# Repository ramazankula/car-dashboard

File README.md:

# Renault Megane 2 Dashboard Panel Prototype for Vehicle Simulator
In this project, a clone of Renault Megane 2 car dashboard panel is designed specially for a vehicle simulator project. It was designed to be compatible with vehicel simulation software.

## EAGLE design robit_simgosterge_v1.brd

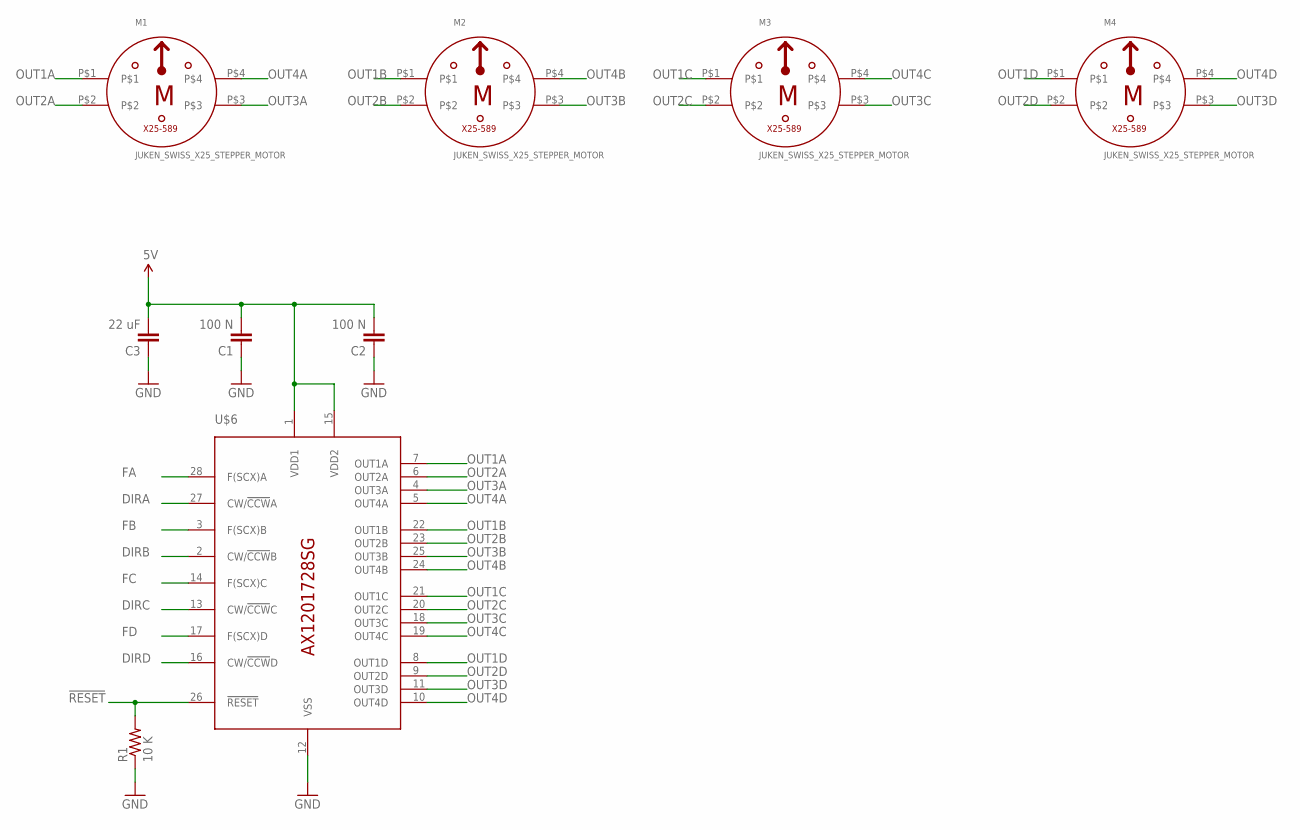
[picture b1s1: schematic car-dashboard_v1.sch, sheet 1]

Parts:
C1, C2: 100 N; C0805
C3: 22 uF; C0805
M1, M2, M3, M4: JUKEN_SWISS_X25_STEPPER_MOTOR; X25_STEPPER_MOTOR
R1: 10 K; 0805
U$6: AX1201728SG-X25_DRIVER; SOL-28

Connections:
5V: C1.2, C2.2, C3.2, U$6.1 (VDD1), U$6.15 (VDD2); also elsewhere on the board
!RESET: R1.2, U$6.26 (!RESET); also elsewhere on the board
DIRA: U$6.27 (CW/!CCW!A); also elsewhere on the board
DIRB: U$6.2 (CW/!CCW!B); also elsewhere on the board
DIRC: U$6.13 (CW/!CCW!C); also elsewhere on the board
DIRD: U$6.16 (CW/!CCW!D); also elsewhere on the board
FA: U$6.28 (F(SCX)A); also elsewhere on the board
FB: U$6.3 (F(SCX)B); also elsewhere on the board
FC: U$6.14 (F(SCX)C); also elsewhere on the board
FD: U$6.17 (F(SCX)D); also elsewhere on the board
GND: C1.1, C2.1, C3.1, R1.1, U$6.12 (VSS); also elsewhere on the board
OUT1A: M1.P$1, U$6.7 (OUT1A)
OUT1B: M2.P$1, U$6.22 (OUT1B)
OUT1C: M3.P$1, U$6.21 (OUT1C)
OUT1D: M4.P$1, U$6.8 (OUT1D)
OUT2A: M1.P$2, U$6.6 (OUT2A)
OUT2B: M2.P$2, U$6.23 (OUT2B)
OUT2C: M3.P$2, U$6.20 (OUT2C)
OUT2D: M4.P$2, U$6.9 (OUT2D)
OUT3A: M1.P$3, U$6.4 (OUT3A)
OUT3B: M2.P$3, U$6.25 (OUT3B)
OUT3C: M3.P$3, U$6.18 (OUT3C)
OUT3D: M4.P$3, U$6.11 (OUT3D)
OUT4A: M1.P$4, U$6.5 (OUT4A)
OUT4B: M2.P$4, U$6.24 (OUT4B)
OUT4C: M3.P$4, U$6.19 (OUT4C)
OUT4D: M4.P$4, U$6.10 (OUT4D)

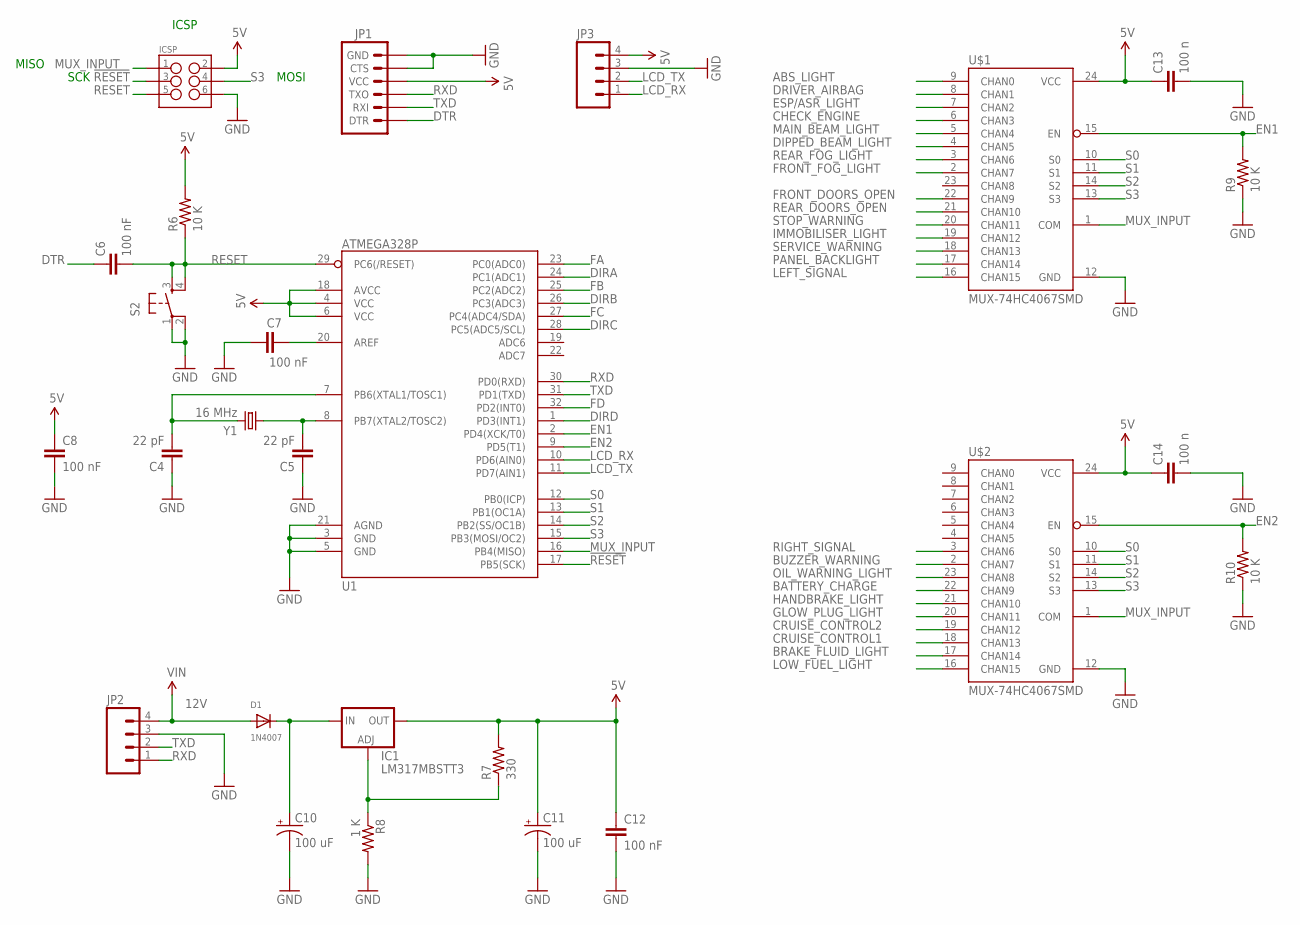
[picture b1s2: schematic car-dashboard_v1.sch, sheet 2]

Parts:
C4, C5: 22 pF; C0805
C6, C7, C8, C12: 100 nF; C0805
C10, C11: 100 uF; PANASONIC_F
C13, C14: 100 n; C0805
D1: 1N4007; SMADIODE
IC1: LM317MBSTT3; SOT223
ICSP: M03X22X3_SILK_SM; 2X3
JP1: ARDUINO_SERIAL_PROGRAMPTH; 1X06
JP2, JP3: M04POLAR; MOLEX-1X4
R6, R9, R10: 10 K; R0805
R7: 330; R0805
R8: 1 K; R0805
S2: TAC_SWITCHPTH; TACTILE-PTH
U1: ATMEGA328P; TQFP32-08
U$1, U$2: MUX-74HC4067SMD; SSOP24
Y1: 16 MHz; HC49UP

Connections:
5V: C8.1, C11.+, C12.1, C13.1, C14.1, IC1.4 (OUT), ICSP.2, JP1.4 (VCC), JP3.4, R6.2, R7.2, U1.4 (VCC), U1.6 (VCC), U1.18 (AVCC), U$1.24 (VCC), U$2.24 (VCC); also elsewhere on the board
12V: D1.A, JP2.4
!RESET: ICSP.3, U1.17 (PB5(SCK)); also elsewhere on the board
ABS_LIGHT: U$1.9 (CHAN0); also elsewhere on the board
BATTERY_CHARGE: U$2.22 (CHAN9); also elsewhere on the board
BRAKE_FLUID_LIGHT: U$2.17 (CHAN14); also elsewhere on the board
BUZZER_WARNING: U$2.2 (CHAN7); also elsewhere on the board
CHECK_ENGINE: U$1.6 (CHAN3); also elsewhere on the board
CRUISE_CONTROL1: U$2.18 (CHAN13); also elsewhere on the board
CRUISE_CONTROL2: U$2.19 (CHAN12); also elsewhere on the board
DIPPED_BEAM_LIGHT: U$1.4 (CHAN5); also elsewhere on the board
DIRA: U1.24 (PC1(ADC1)); also elsewhere on the board
DIRB: U1.26 (PC3(ADC3)); also elsewhere on the board
DIRC: U1.28 (PC5(ADC5/SCL)); also elsewhere on the board
DIRD: U1.1 (PD3(INT1)); also elsewhere on the board
DRIVER_AIRBAG: U$1.8 (CHAN1); also elsewhere on the board
DTR: C6.1, JP1.1 (DTR)
EN1: R9.2, U1.2 (PD4(XCK/T0)), U$1.15 (EN)
EN2: R10.2, U1.9 (PD5(T1)), U$2.15 (EN)
ESP/ASR_LIGHT: U$1.7 (CHAN2); also elsewhere on the board
FA: U1.23 (PC0(ADC0)); also elsewhere on the board
FB: U1.25 (PC2(ADC2)); also elsewhere on the board
FC: U1.27 (PC4(ADC4/SDA)); also elsewhere on the board
FD: U1.32 (PD2(INT0)); also elsewhere on the board
FRONT_DOORS_OPEN: U$1.22 (CHAN9); also elsewhere on the board
FRONT_FOG_LIGHT: U$1.2 (CHAN7); also elsewhere on the board
GLOW_PLUG_LIGHT: U$2.20 (CHAN11); also elsewhere on the board
GND: C4.1, C5.1, C7.1, C8.2, C10.-, C11.-, C12.2, C13.2, C14.2, ICSP.6, JP1.5 (CTS), JP1.6 (GND), JP2.3, JP3.3, R8.2, R9.1, R10.1, S2.1, S2.2, U1.3 (GND), U1.5 (GND), U1.21 (AGND), U$1.12 (GND), U$2.12 (GND); also elsewhere on the board
HANDBRAKE_LIGHT: U$2.21 (CHAN10); also elsewhere on the board
IMMOBILISER_LIGHT: U$1.19 (CHAN12); also elsewhere on the board
LCD_RX: JP3.1, U1.10 (PD6(AIN0))
LCD_TX: JP3.2, U1.11 (PD7(AIN1))
LEFT_SIGNAL: U$1.16 (CHAN15); also elsewhere on the board
LOW_FUEL_LIGHT: U$2.16 (CHAN15); also elsewhere on the board
MAIN_BEAM_LIGHT: U$1.5 (CHAN4); also elsewhere on the board
MUX_INPUT: ICSP.1, U1.16 (PB4(MISO)), U$1.1 (COM), U$2.1 (COM)
unnamed: C4.2, U1.7 (PB6(XTAL1/TOSC1)), Y1.2
unnamed: C5.2, U1.8 (PB7(XTAL2/TOSC2)), Y1.1
unnamed: C10.+, D1.C, IC1.3 (IN)
unnamed: C7.2, U1.20 (AREF)
unnamed: IC1.1 (ADJ), R7.1, R8.1
OIL_WARNING_LIGHT: U$2.23 (CHAN8); also elsewhere on the board
PANEL_BACKLIGHT: U$1.17 (CHAN14); also elsewhere on the board
REAR_DOORS_OPEN: U$1.21 (CHAN10); also elsewhere on the board
REAR_FOG_LIGHT: U$1.3 (CHAN6); also elsewhere on the board
RESET: C6.2, ICSP.5, R6.1, S2.3, S2.4, U1.29 (PC6(/RESET))
RIGHT_SIGNAL: U$2.3 (CHAN6); also elsewhere on the board
RXD: JP1.3 (TXO), JP2.1, U1.30 (PD0(RXD))
S0: U1.12 (PB0(ICP)), U$1.10 (S0), U$2.10 (S0)
S1: U1.13 (PB1(OC1A)), U$1.11 (S1), U$2.11 (S1)
S2: U1.14 (PB2(SS/OC1B)), U$1.14 (S2), U$2.14 (S2)
S3: ICSP.4, U1.15 (PB3(MOSI/OC2)), U$1.13 (S3), U$2.13 (S3)
SERVICE_WARNING: U$1.18 (CHAN13); also elsewhere on the board
STOP_WARNING: U$1.20 (CHAN11); also elsewhere on the board
TXD: JP1.2 (RXI), JP2.2, U1.31 (PD1(TXD))

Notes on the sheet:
SCK
MISO
MOSI
ICSP

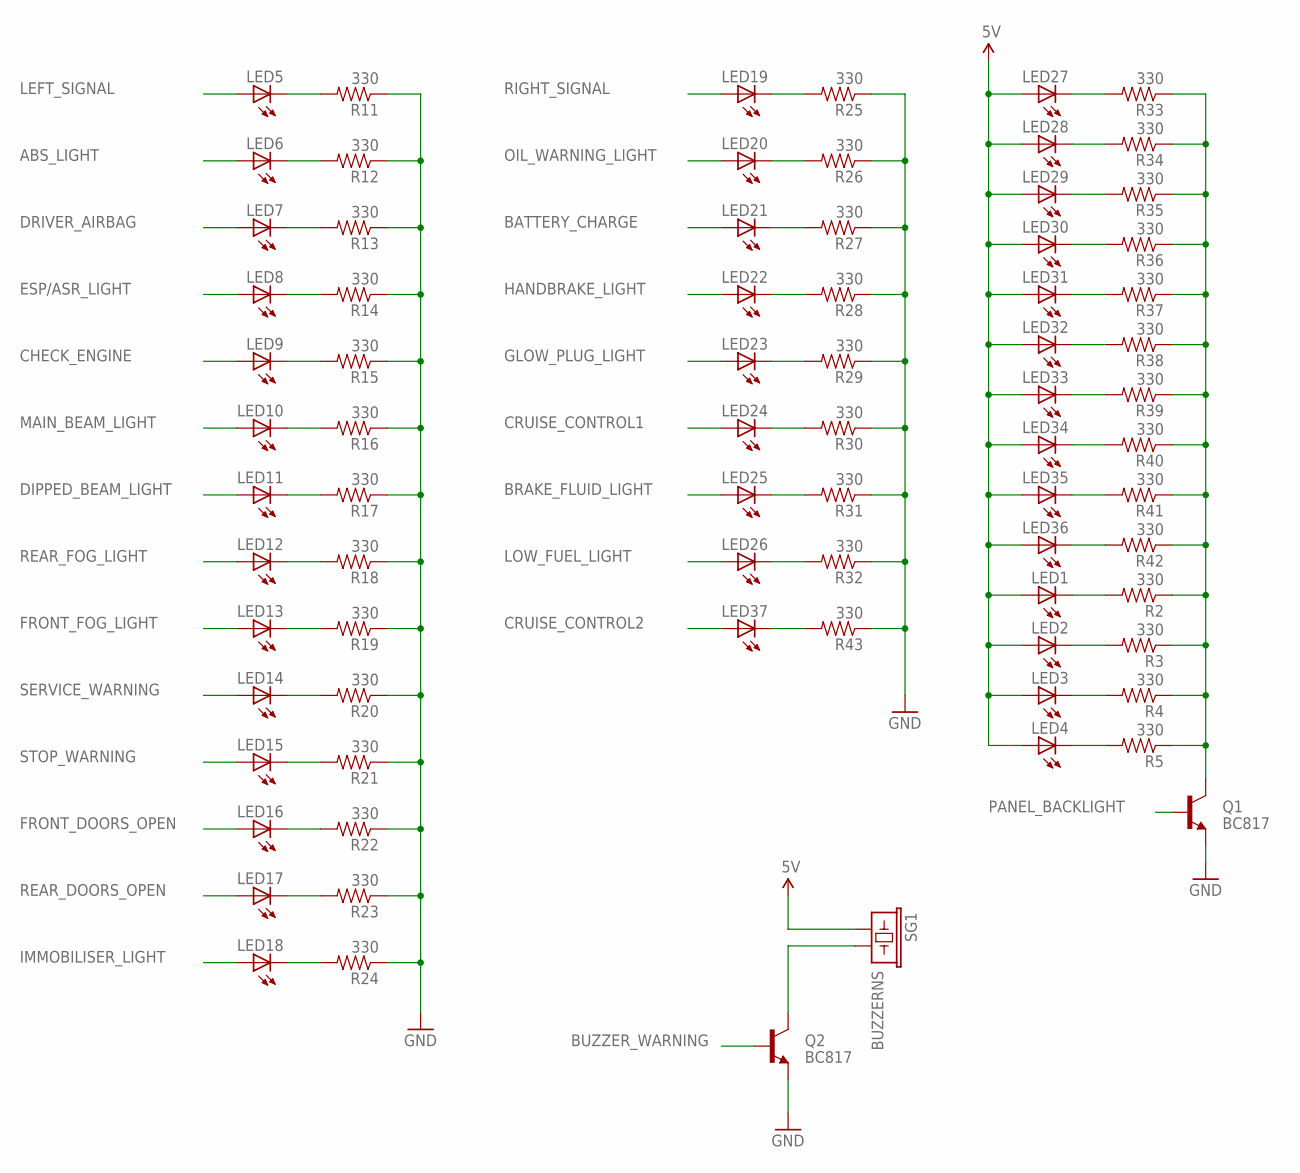
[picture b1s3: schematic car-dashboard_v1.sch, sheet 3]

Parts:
LED1, LED2, LED3, LED4, LED5, LED6, LED7, LED8, LED9, LED10, LED11, LED12, LED13, LED14, LED15, LED16, LED17, LED18, LED19, LED20, LED21, LED22, LED23, LED24, LED25, LED26, LED27, LED28, LED29, LED30, LED31, LED32, LED33, LED34, LED35, LED36, LED37: LEDCHIPLED_0805; CHIPLED_0805
Q1, Q2: BC817; SOT23-3
R2, R3, R4, R5, R11, R12, R13, R14, R15, R16, R17, R18, R19, R20, R21, R22, R23, R24, R25, R26, R27, R28, R29, R30, R31, R32, R33, R34, R35, R36, R37, R38, R39, R40, R41, R42, R43: 330; 0805
SG1: BUZZERNS; BUZZER-12MM-NS

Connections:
5V: LED1.A, LED2.A, LED3.A, LED4.A, LED27.A, LED28.A, LED29.A, LED30.A, LED31.A, LED32.A, LED33.A, LED34.A, LED35.A, LED36.A, SG1.+ (1); also elsewhere on the board
ABS_LIGHT: LED6.A; also elsewhere on the board
BATTERY_CHARGE: LED21.A; also elsewhere on the board
BRAKE_FLUID_LIGHT: LED25.A; also elsewhere on the board
BUZZER_WARNING: Q2.1 (B); also elsewhere on the board
CHECK_ENGINE: LED9.A; also elsewhere on the board
CRUISE_CONTROL1: LED24.A; also elsewhere on the board
CRUISE_CONTROL2: LED37.A; also elsewhere on the board
DIPPED_BEAM_LIGHT: LED11.A; also elsewhere on the board
DRIVER_AIRBAG: LED7.A; also elsewhere on the board
ESP/ASR_LIGHT: LED8.A; also elsewhere on the board
FRONT_DOORS_OPEN: LED16.A; also elsewhere on the board
FRONT_FOG_LIGHT: LED13.A; also elsewhere on the board
GLOW_PLUG_LIGHT: LED23.A; also elsewhere on the board
GND: Q1.2 (E), Q2.2 (E), R11.1, R12.1, R13.1, R14.1, R15.1, R16.1, R17.1, R18.1, R19.1, R20.1, R21.1, R22.1, R23.1, R24.1, R25.1, R26.1, R27.1, R28.1, R29.1, R30.1, R31.1, R32.1, R43.1; also elsewhere on the board
HANDBRAKE_LIGHT: LED22.A; also elsewhere on the board
IMMOBILISER_LIGHT: LED18.A; also elsewhere on the board
LEFT_SIGNAL: LED5.A; also elsewhere on the board
LOW_FUEL_LIGHT: LED26.A; also elsewhere on the board
MAIN_BEAM_LIGHT: LED10.A; also elsewhere on the board
unnamed: LED1.C, R2.2
unnamed: LED2.C, R3.2
unnamed: LED3.C, R4.2
unnamed: LED4.C, R5.2
unnamed: LED5.C, R11.2
unnamed: LED6.C, R12.2
unnamed: LED7.C, R13.2
unnamed: LED8.C, R14.2
unnamed: LED9.C, R15.2
unnamed: LED10.C, R16.2
unnamed: LED11.C, R17.2
unnamed: LED12.C, R18.2
unnamed: LED37.C, R43.2
unnamed: LED13.C, R19.2
unnamed: LED14.C, R20.2
unnamed: LED15.C, R21.2
unnamed: LED16.C, R22.2
unnamed: LED17.C, R23.2
unnamed: LED18.C, R24.2
unnamed: LED19.C, R25.2
unnamed: LED20.C, R26.2
unnamed: LED21.C, R27.2
unnamed: LED22.C, R28.2
unnamed: LED23.C, R29.2
unnamed: LED24.C, R30.2
unnamed: LED25.C, R31.2
unnamed: LED26.C, R32.2
unnamed: LED27.C, R33.2
unnamed: LED28.C, R34.2
unnamed: LED29.C, R35.2
unnamed: LED30.C, R36.2
unnamed: LED31.C, R37.2
unnamed: Q1.3 (C), R2.1, R3.1, R4.1, R5.1, R33.1, R34.1, R35.1, R36.1, R37.1, R38.1, R39.1, R40.1, R41.1, R42.1
unnamed: LED32.C, R38.2
unnamed: LED33.C, R39.2
unnamed: LED34.C, R40.2
unnamed: LED35.C, R41.2
unnamed: LED36.C, R42.2
unnamed: Q2.3 (C), SG1.- (2)
OIL_WARNING_LIGHT: LED20.A; also elsewhere on the board
PANEL_BACKLIGHT: Q1.1 (B); also elsewhere on the board
REAR_DOORS_OPEN: LED17.A; also elsewhere on the board
REAR_FOG_LIGHT: LED12.A; also elsewhere on the board
RIGHT_SIGNAL: LED19.A; also elsewhere on the board
SERVICE_WARNING: LED14.A; also elsewhere on the board
STOP_WARNING: LED15.A; also elsewhere on the board

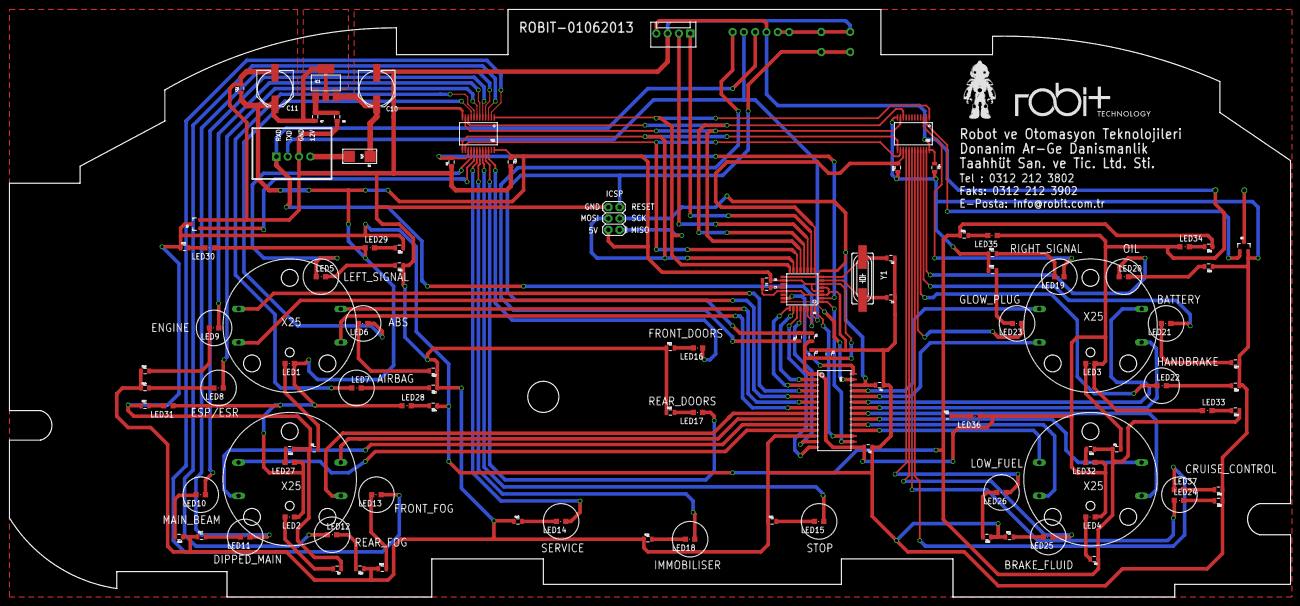
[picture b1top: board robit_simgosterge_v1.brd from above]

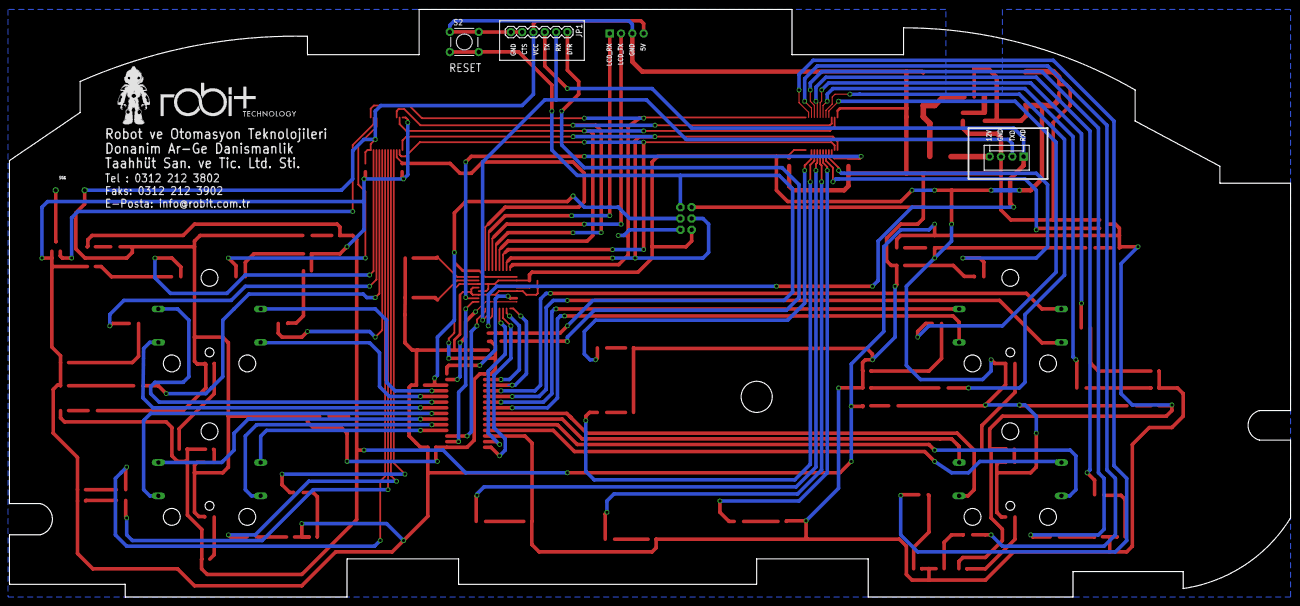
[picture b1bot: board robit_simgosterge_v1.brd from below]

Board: 2 copper layers, 288.0 x 132.1 mm, 116 parts (5 on the bottom side), 110 nets.

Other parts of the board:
U$3: ROBIT_ROBOT_BP
U$4: ROBIT_ROBOT
U$5, U$7: ROBIT_LOGO

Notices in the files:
parts and their libraries:
SparkFun-Aesthetics: Licensing: CC v3.0 Share-Alike You are welcome to use this library for commercial purposes.
